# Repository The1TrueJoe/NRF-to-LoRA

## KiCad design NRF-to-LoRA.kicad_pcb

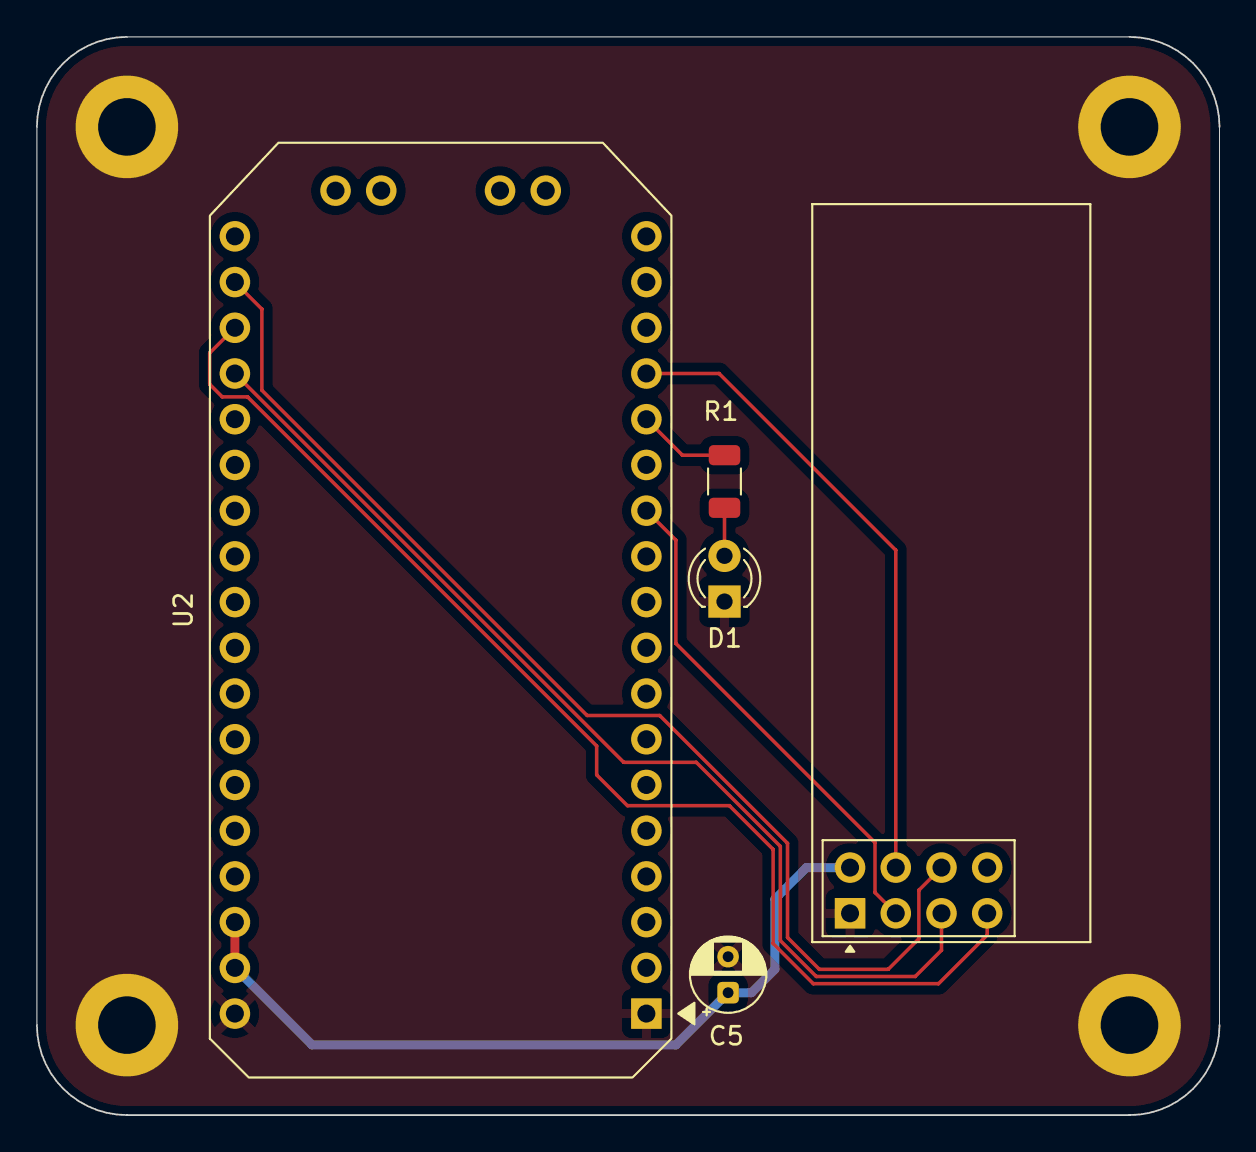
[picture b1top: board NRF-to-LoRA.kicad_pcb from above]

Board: 2 copper layers, 65.7 x 59.9 mm, 9 parts (0 on the bottom side), 9 nets.

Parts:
C5: 10uF; CP_Radial_D4.0mm_P2.00mm
D1: LED; LED_D3.0mm
H1, H2, H3, H4: MountingHole_Pad; MountingHole_3.2mm_M3_ISO7380_Pad
R1: 220; R_1206_3216Metric
U1: NRF24L01_Breakout; nRF24L01_PA_LNA_Breakout
U2: Heltec_WiFi_LoRa32_V4

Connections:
+3V3: C5.1, U1.2 (VCC), U2.20 (3V3), U2.21 (3V3)
GND: C5.2, D1.1 (K), H1.1, H2.1, H3.1, H4.1, U1.1 (GND), U2.1 (GND), U2.19 (GND)
unnamed: D1.2 (A), R1.1
unnamed: U1.3 (CE), U2.12 (GPIO33)
unnamed: U1.7 (MISO), U2.34 (GPIO5)
unnamed: U1.6 (MOSI), U2.35 (GPIO6)
unnamed: U1.5 (SCK), U2.33 (GPIO4)
unnamed: U1.4 (~CSN), U2.15 (GPIO26)
unnamed: R1.2, U2.14 (GPIO48)
